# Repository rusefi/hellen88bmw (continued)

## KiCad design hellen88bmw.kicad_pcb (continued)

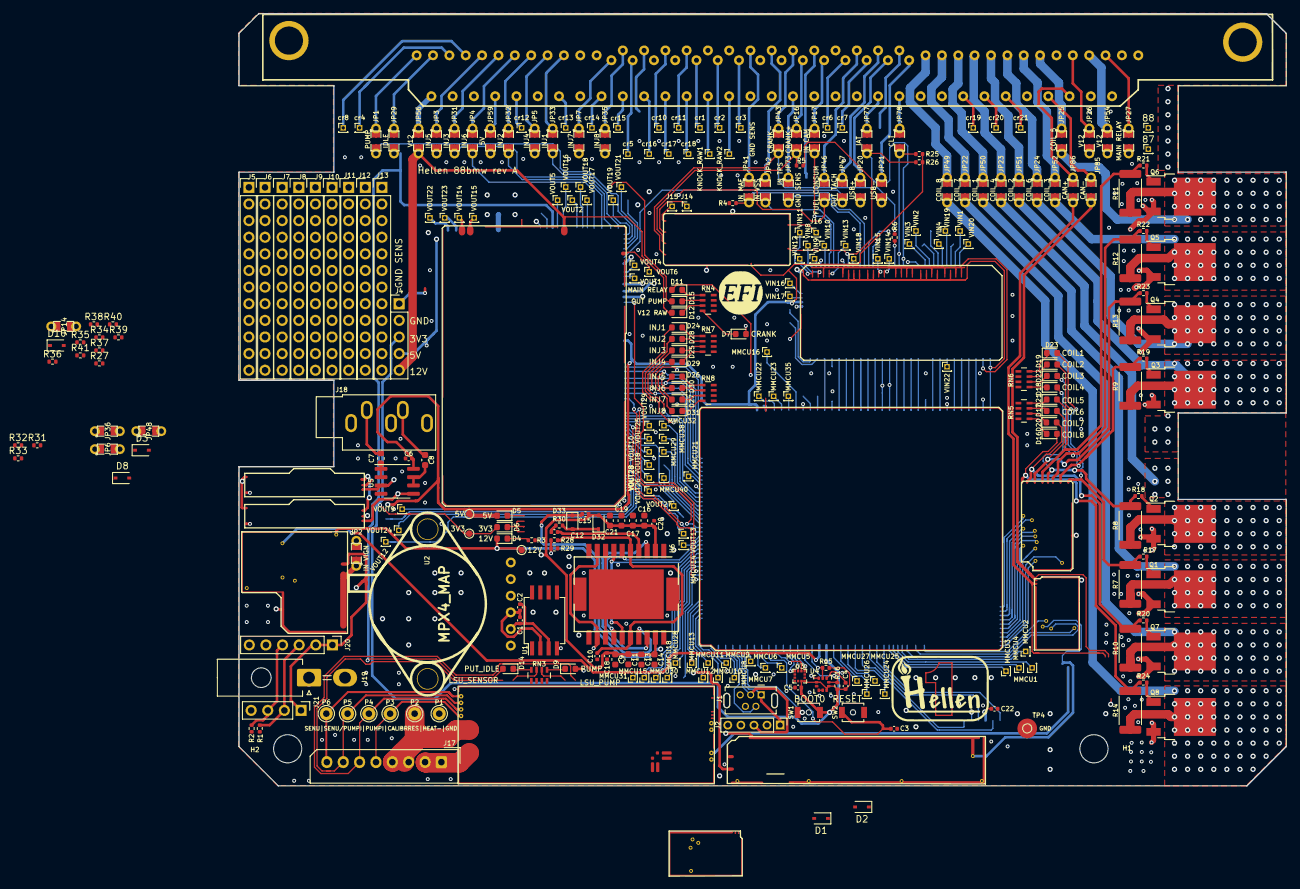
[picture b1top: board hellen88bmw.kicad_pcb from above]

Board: 4 copper layers, 160.0 x 118.0 mm, 306 parts (1 on the bottom side), 328 nets.

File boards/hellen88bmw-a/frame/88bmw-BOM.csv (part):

Comment,Designator,Footprint,LCSC Part #
"100nF","C1","C0402","C105882"
"100nF","C2","C0402","C105882"
"100nF","C3","C0402","C105882"
"100nF","C4","C0402","C105882"
"100nF","C5","C0402","C105882"
"100nF","C6","C0402","C105882"
"10uF","C7","C0603","C87152"
"10uF","C8","C0603","C87152"
"10uF","C9","C0603","C87152"
"5.6nF","C10","C0402","C115688"
"10uF","C11","C0603","C87152"
"10nF","C12","C0402","C541443"
"10uF","C13","C0603","C87152"
"10uF","C14","C0603","C87152"
"220nF","C15","C0402","C106258"
"10uF","C16","C0603","C87152"
"10uF","C17","C0603","C87152"
"100nF","C18","C0402","C105882"
"10uF","C19","C0603","C87152"
"100nF","C20","C0402","C105882"
"10uF","C21","C0603","C87152"
"100nF","C22","C0402","C105882"
"cr","cr1","PinHeader_1x01_P1.00mm_Vertical",""
"cr","cr2","PinHeader_1x01_P1.00mm_Vertical",""
"cr","cr3","PinHeader_1x01_P1.00mm_Vertical",""
"cr","cr4","PinHeader_1x01_P1.00mm_Vertical",""
"cr","cr5","PinHeader_1x01_P1.00mm_Vertical",""
"cr","cr6","PinHeader_1x01_P1.00mm_Vertical",""
"cr","cr7","PinHeader_1x01_P1.00mm_Vertical",""
"cr","cr8","PinHeader_1x01_P1.00mm_Vertical",""
"cr","cr9","PinHeader_1x01_P1.00mm_Vertical",""
"cr","cr10","PinHeader_1x01_P1.00mm_Vertical",""
"cr","cr11","PinHeader_1x01_P1.00mm_Vertical",""
"cr","cr12","PinHeader_1x01_P1.00mm_Vertical",""
"cr","cr13","PinHeader_1x01_P1.00mm_Vertical",""
"cr","cr14","PinHeader_1x01_P1.00mm_Vertical",""
"cr","cr15","PinHeader_1x01_P1.00mm_Vertical",""
"cr","cr16","PinHeader_1x01_P1.00mm_Vertical",""
"cr","cr17","PinHeader_1x01_P1.00mm_Vertical",""
"cr","cr18","PinHeader_1x01_P1.00mm_Vertical",""
"cr","cr19","PinHeader_1x01_P1.00mm_Vertical",""
"cr","cr20","PinHeader_1x01_P1.00mm_Vertical",""
"cr","cr21","PinHeader_1x01_P1.00mm_Vertical",""
"cr","cr22","PinHeader_1x01_P1.00mm_Vertical",""
"cr","cr23","PinHeader_1x01_P1.00mm_Vertical",""
"cr","cr24","PinHeader_1x01_P1.00mm_Vertical",""
"LED-BLUE-0603","D1","LED-0603","C72041"
"LED-BLUE-0603","D2","LED-0603","C72041"
"LED-GREEN-0603","D4","LED-0603","C72043"
"LED-GREEN-0603","D5","LED-0603","C72043"
"LED-GREEN-0603","D6","LED-0603","C72043"
"LED-WHITE-0603","D7","LED-0603","C84265"
"LED-BLUE-0603","D9","LED-0603","C72041"
"LED-BLUE-0603","D10","LED-0603","C72041"
"LED-RED-0603","D11","LED-0603","C2286"
"LED-GREEN-0603","D12","LED-0603","C72043"
"LED-BLUE-0603","D13","LED-0603","C72041"
"LED-BLUE-0603","D14","LED-0603","C72041"
"LED-RED-0603","D15","LED-0603","C2286"
"LED-BLUE-0603","D16","LED-0603","C72041"
"LED-BLUE-0603","D17","LED-0603","C72041"
"LED-BLUE-0603","D18","LED-0603","C72041"
"LED-BLUE-0603","D19","LED-0603","C72041"
"LED-BLUE-0603","D20","LED-0603","C72041"
"LED-BLUE-0603","D21","LED-0603","C72041"
"LED-BLUE-0603","D22","LED-0603","C72041"
"LED-BLUE-0603","D23","LED-0603","C72041"
"LED-RED-0603","D24","LED-0603","C2286"
"LED-RED-0603","D25","LED-0603","C2286"
"LED-RED-0603","D26","LED-0603","C2286"
"LED-RED-0603","D27","LED-0603","C2286"
"LED-RED-0603","D28","LED-0603","C2286"
"LED-RED-0603","D29","LED-0603","C2286"
"LED-RED-0603","D30","LED-0603","C2286"
"LED-RED-0603","D31","LED-0603","C2286"
"1N4148WS","D32","D_SOD-323","C2128"
"1N4148WS","D33","D_SOD-323","C2128"
"Conn_01x01","G1","LOGO",""
"Conn_01x01","G2","LOGO",""
"MountingHole","H1","MountingHole_4.3mm_M4_DIN965",""
"MountingHole","H2","MountingHole_4.3mm_M4_DIN965",""
"920-462A2021Y10101","J1","USB-MINI-B-VERTICAL","C13453"
"UB-20PMFP-LC7002","J2","PinHeader_1x05_P2.00mm_Vertical","DNP"
"Micro_SD_Card","J3","693072010801",""
"Conn_01x05","J4","PinHeader_1x05_P2.54mm_Vertical",""
"Conn_01x12","J5","PinHeader_1x12_P2.54mm_Vertical",""
"Conn_01x12","J6","PinHeader_1x12_P2.54mm_Vertical",""
"Conn_01x12","J7","PinHeader_1x12_P2.54mm_Vertical",""
"Conn_01x12","J8","PinHeader_1x12_P2.54mm_Vertical",""
"Conn_01x12","J9","PinHeader_1x12_P2.54mm_Vertical",""
"Conn_01x12","J10","PinHeader_1x12_P2.54mm_Vertical",""
"Conn_01x12","J11","PinHeader_1x12_P2.54mm_Vertical",""
"Conn_01x12","J12","PinHeader_1x12_P2.54mm_Vertical",""
"Conn_01x12","J13","PinHeader_1x12_P2.54mm_Vertical",""
"VRIN1","J14","PinHeader_1x01_P1.00mm_Vertical",""
"VRIN2","J15","PinHeader_1x01_P1.00mm_Vertical",""
"VROUT1","J16","PinHeader_1x01_P1.00mm_Vertical",""
"XH-8A","J17","XH-8A","C10385"
"PJ-3250-5A","J18","Jack_3.5mm_CUI_SJ1-3535NG_Horizontal","C165947"
"MiniFit","J19","Molex_Mini-Fit_Jr_5569-02A2_2x01_P4.20mm_Horizontal",""
"ETB","J20","PinHeader_1x06_P2.54mm_Vertical","C343639"
"ETB","J21","PinHeader_1x04_P2.54mm_Vertical","C343639"
"Jumper_2_Open","JP1","SM0805_jumper","C17477"
"Jumper_2_Open","JP2","SM0805_jumper","C17477"
"Jumper_2_Open","JP3","SM0805_jumper","C17477"
"Jumper_2_Open","JP4","SM0805_jumper","C17477"
"Jumper_2_Open","JP5","SM0805_jumper","C17477"
"Jumper_2_Open","JP7","SM0805_jumper","C17477"
"Jumper_2_Open","JP14","SM0805_jumper","C17477"
"Jumper_2_Open","JP16","SM0805_jumper","C17477"
"Jumper_2_Open","JP17","SM0805_jumper","C17477"
"Jumper_2_Open","JP20","SM0805_jumper","C17477"
"Jumper_2_Open","JP21","SM0805_jumper","C17477"
"Jumper_2_Open","JP22","SM0805_jumper","C17477"
"Jumper_2_Open","JP23","SM0805_jumper","C17477"
"Jumper_2_Open","JP24","SM0805_jumper","C17477"
"Jumper_2_Open","JP25","SM0805_jumper","C17477"
"Jumper_2_Open","JP26","SM0805_jumper","C17477"
"Jumper_2_Open","JP27","SM0805_jumper","C17477"
"Jumper_2_Open","JP29","SM0805_jumper","C17477"
"Jumper_2_Open","JP31","SM0805_jumper","C17477"
"Jumper_2_Open","JP32","SM0805_jumper","C17477"
"Jumper_2_Open","JP33","SM0805_jumper","C17477"
"Jumper_2_Open","JP35","SM0805_jumper","C17477"
"Jumper_2_Open","JP41","SM0805_jumper","C17477"
"Jumper_2_Open","JP42","SM0805_jumper","C17477"
"Jumper_2_Open","JP43","SM0805_jumper","C17477"
"Jumper_2_Open","JP44","SM0805_jumper","C17477"
"Jumper_2_Open","JP46","SM0805_jumper","C17477"
"Jumper_2_Open","JP47","SM0805_jumper","C17477"
"Jumper_2_Open","JP49","SM0805_jumper","C17477"
"Jumper_2_Open","JP50","SM0805_jumper","C17477"
"Jumper_2_Open","JP51","SM0805_jumper","C17477"
"Jumper_2_Open","JP52","SM0805_jumper","C17477"
"Jumper_2_Open","JP54","SM0805_jumper","C17477"
"Jumper_2_Open","JP56","SM0805_jumper","C17477"
"Jumper_2_Open","JP59","SM0805_jumper","C17477"
"Jumper_2_Open","JP73","SM0805_jumper","C17477"
"Jumper_2_Open","JP77","SM0805_jumper","C17477"
"Jumper_2_Open","JP78","SM0805_jumper","C17477"
"Jumper_2_Open","JP85","SM0805_jumper","C17477"
"Jumper_2_Open","JP86","SM0805_jumper","C17477"
"IN_KNOCK1_RAW","KNOCK_RAW1","PinHeader_1x01_P1.00mm_Vertical",""
"IN_KNOCK2_RAW","KNOCK_RAW2","PinHeader_1x01_P1.00mm_Vertical",""
"Module:power12/0.2","M1","power12",""
"Module:can/0.1","M2","can",""
"Module:wbo/0.2","M3","wbo",""
"Module:can/0.1","M4","can",""
"Module:power5/0.2","M5","power5",""
"Module:vr/0.1","M6","vr",""
"Module:input/0.1","M7","input",""
"Module:knock/0.1","M8","knock",""
"Module:output/0.2","M9","output",""
"Module:ign8/0.1","M10","ign8",""
"Module:mcu144/0.5","M11","mcu",""
"Module:knock/0.1","M12","knock",""
"MMCU","MMCU1","PinHeader_1x01_P1.00mm_Vertical",""
"MMCU","MMCU2","PinHeader_1x01_P1.00mm_Vertical",""
"MMCU","MMCU3","PinHeader_1x01_P1.00mm_Vertical",""
"MMCU","MMCU4","PinHeader_1x01_P1.00mm_Vertical",""
"MMCU","MMCU5","PinHeader_1x01_P1.00mm_Vertical",""
"MMCU","MMCU6","PinHeader_1x01_P1.00mm_Vertical",""
"MMCU","MMCU7","PinHeader_1x01_P1.00mm_Vertical",""
"MMCU","MMCU8","PinHeader_1x01_P1.00mm_Vertical",""
"MMCU","MMCU9","PinHeader_1x01_P1.00mm_Vertical",""
"MMCU","MMCU10","PinHeader_1x01_P1.00mm_Vertical",""
"MMCU","MMCU11","PinHeader_1x01_P1.00mm_Vertical",""
"MMCU","MMCU12","PinHeader_1x01_P1.00mm_Vertical",""
"MMCU","MMCU13","PinHeader_1x01_P1.00mm_Vertical",""
"MMCU","MMCU14","PinHeader_1x01_P1.00mm_Vertical",""
"MMCU","MMCU15","PinHeader_1x01_P1.00mm_Vertical",""
"MMCU","MMCU16","PinHeader_1x01_P1.00mm_Vertical",""
"MMCU","MMCU17","PinHeader_1x01_P1.00mm_Vertical",""
"MMCU","MMCU18","PinHeader_1x01_P1.00mm_Vertical",""
"MMCU","MMCU19","PinHeader_1x01_P1.00mm_Vertical",""
"MMCU","MMCU21","PinHeader_1x01_P1.00mm_Vertical",""
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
